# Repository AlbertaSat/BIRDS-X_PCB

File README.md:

# JASPER BIRDS-X PCB
Repository for the PCB design for the JASPER BIRDS-X project.

JASPER is a joint organization between the University of Alberta's AlbertaSat and the University of Calgary's CalgaryToSpace cubesat teams.

## Features
1. Capable of APRS (Automated Packet Reporting System) digipeat and store-and-forward modes, and periodic beaconing, for use by Amateur Radio enthusiasts.
2. Implements a radiation experiment, which compares the radiation shielding properties of shielding options.
	* Uses RADFET sensors as radiation detection sensors.
	* Uses linear CCD sensor (painted black) to sense galactic cosmic rays.
3. Employs power safety systems (over-current protection, enable pins, etc.) to interface with the BIRDS-X satellite parent system.
4. Uses <300 mW on receive, and <1750 mW on transmit.
5. ~~Stores data in flash memory.~~
6. Interfaces with the Mission Boss system via UART.
7. A test fixture board makes flashing and debugging the main payload board easier and more reliable.

## System Block Diagram

## Release Notes
See the [GitHub Releases](https://github.com/AlbertaSat/BIRDS-X_PCB/releases) for this repo.

## License

This repository is licensed under the "CERN Open Hardware Licence Version 2 - Permissive (CERN OHL v2 Permissive)" license. For more information, see [the choosealicense.com description of the license](https://choosealicense.com/licenses/cern-ohl-p-2.0/).

> CERN OHL v2 Permissive
> A permissive license for hardware designs, with conditions only requiring preservation of notices. Contributors provide an express grant of patent rights. Licensed works, modifications, and larger works may be distributed under different terms and without sources.

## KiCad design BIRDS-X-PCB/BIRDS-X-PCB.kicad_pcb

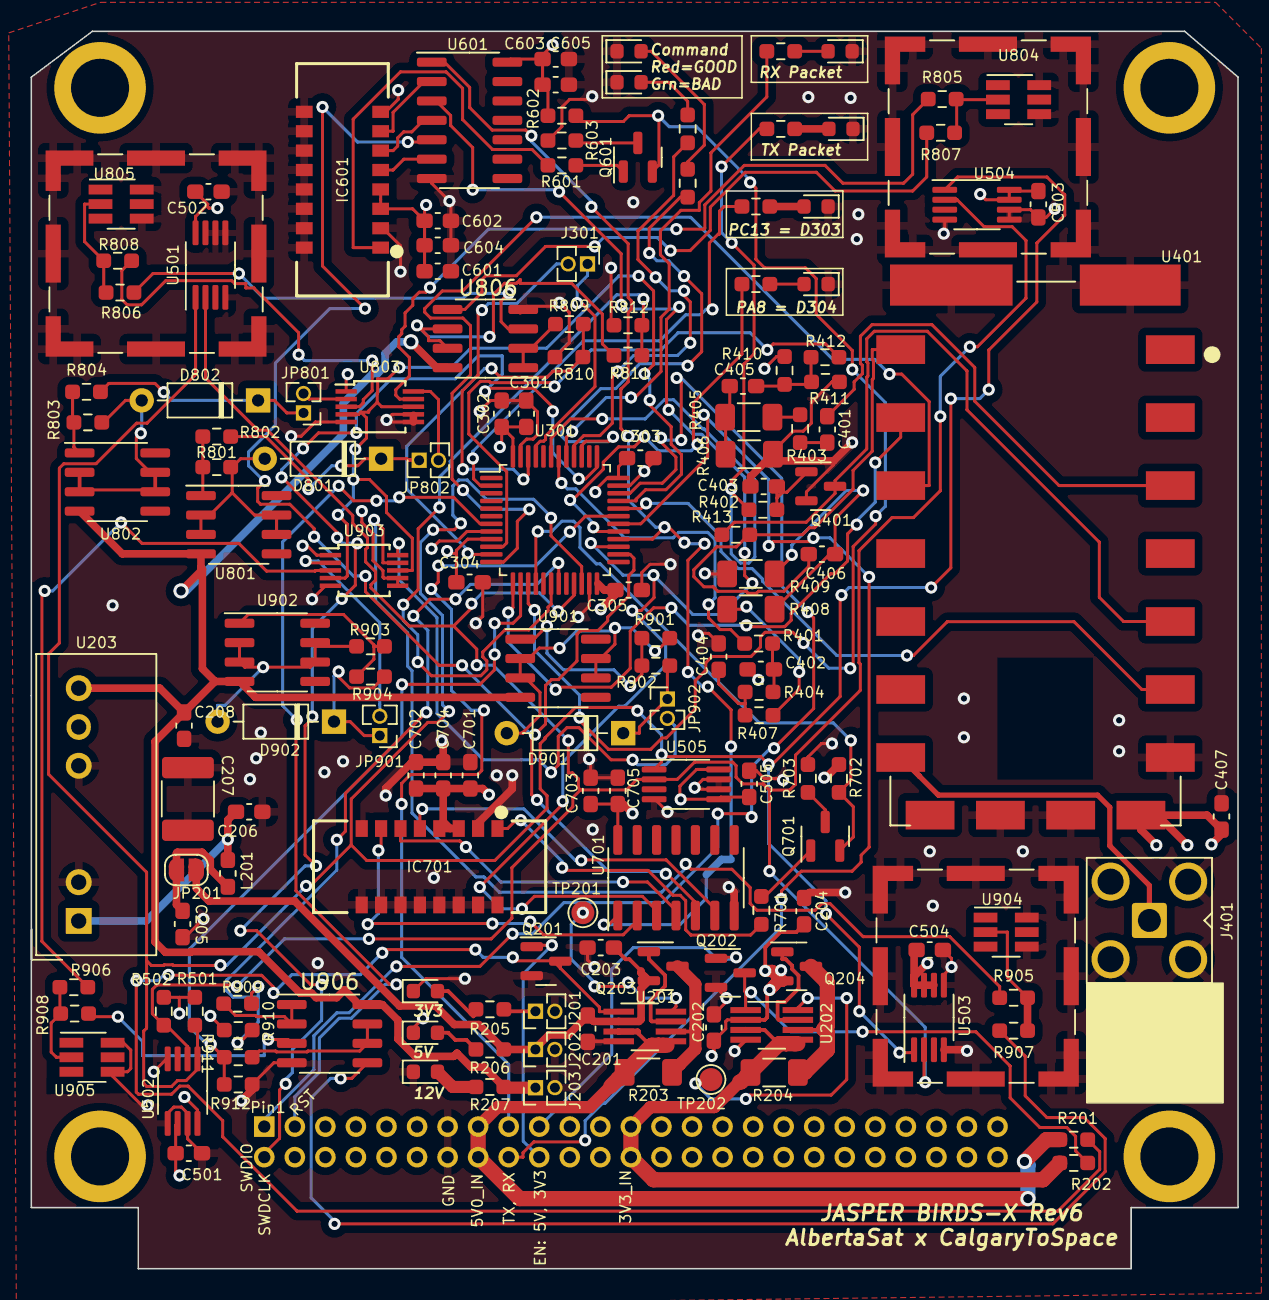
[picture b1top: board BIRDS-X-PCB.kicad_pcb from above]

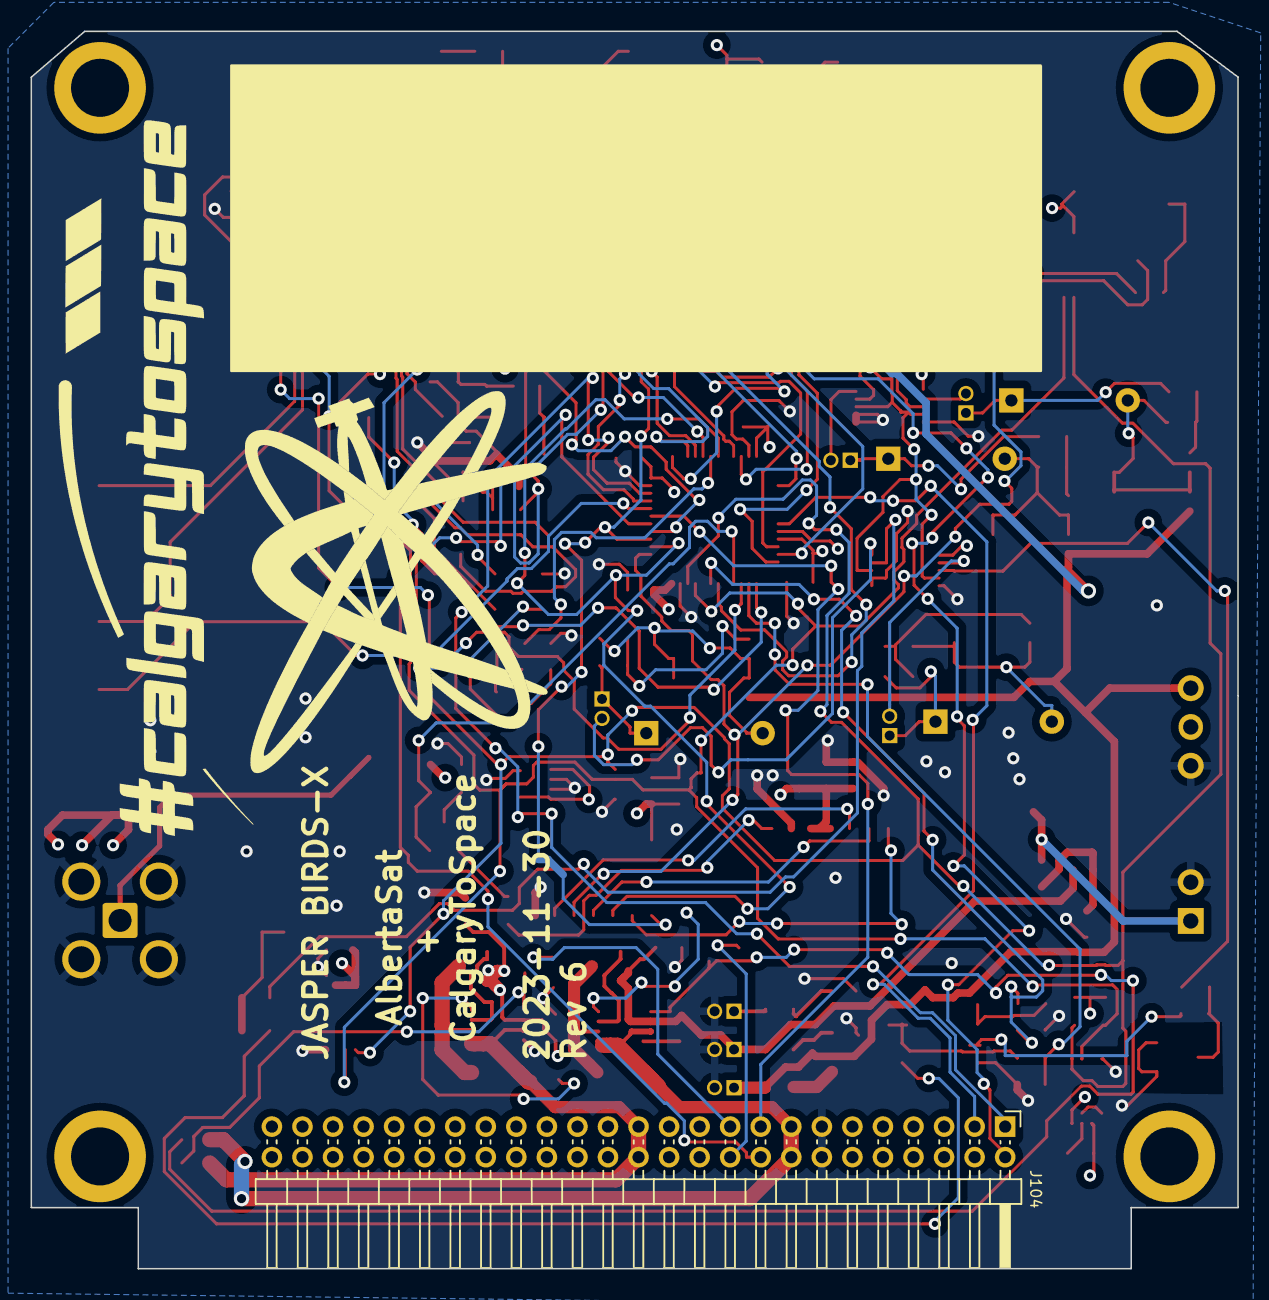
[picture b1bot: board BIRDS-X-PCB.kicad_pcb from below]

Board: 4 copper layers, 79.0 x 81.0 mm, 162 parts (3 on the bottom side), 114 nets.

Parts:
C201, C202, C601, C701: 10u; C_0603_1608Metric_Pad1.08x0.95mm_HandSolder
C203, C204: 1u; C_0603_1608Metric_Pad1.08x0.95mm_HandSolder
C205, C206, C302: 4.7u; C_0603_1608Metric_Pad1.08x0.95mm_HandSolder
C207: 1n; C_1812_4532Metric
C208: 2.2u; C_0603_1608Metric_Pad1.08x0.95mm_HandSolder
C301, C303, C304, C305, C401, C402, C404, C405, C406, C407, C501, C502, C503, C504, C505: 100n; C_0603_1608Metric_Pad1.08x0.95mm_HandSolder
C403: 10n; C_0603_1608Metric_Pad1.08x0.95mm_HandSolder
C602, C603, C702, C703: 0.1u; C_0603_1608Metric_Pad1.08x0.95mm_HandSolder
C604, C605, C704, C705: 0.01u; C_0603_1608Metric_Pad1.08x0.95mm_HandSolder
D201, D202, D203, D301, D302, D303, D304: LED; LED_0603_1608Metric
D801, D802, D901, D902: 1N457; D_DO-35_SOD27_P7.62mm_Horizontal
D_RX301: LED; LED_0603_1608Metric
D_TX301: LED; LED_0603_1608Metric
H101, H102, H103, H104: MountingHole; MountingHole_3.8mm
H105: Logo; AlbertaSat_Logo_25x20mm
H106: Logo; CTS_Logo_50x25mm
IC601, IC701: TCD1103GFG_8Z,AA2_; TCD1103GFG8ZAA2
J101, J102, J103: RFShield_OnePiece; Laird_Technologies_BMI-S-101_13.66x12.70mm
J104: LPC-50M2LG; PinHeader_2x25_P2.00mm_Horizontal
J201, J202, J203, J301: Conn_01x02; PinHeader_1x02_P1.27mm_Vertical
J401: 60611002111501; SMA_Amphenol_901-143_Horizontal_Modified
JP201: Jumper_2_Open; SolderJumper-2_P1.3mm_Open_RoundedPad1.0x1.5mm
JP801, JP802, JP901, JP902: Jumper_2_Open; PinHeader_1x02_P1.27mm_Vertical
L201: 6.8uH; L_0603_1608Metric_Pad1.05x0.95mm_HandSolder
Q201, Q202: 2N7002; SOT-23
Q203, Q204: AO3420; SOT-23
Q401: BC847; SOT-23
Q601, Q701: 2SA1015; SOT-23
R201, R202, R802, R804, R902, R904: 110k; R_0603_1608Metric_Pad0.98x0.95mm_HandSolder
R203: 0.51; R_1206_3216Metric_Pad1.30x1.75mm_HandSolder
R204: 0.075; R_1206_3216Metric_Pad1.30x1.75mm_HandSolder
R205, R501, R502: 3k3; R_0603_1608Metric_Pad0.98x0.95mm_HandSolder
R206: 5.1k; R_0603_1608Metric_Pad0.98x0.95mm_HandSolder
R207: 51k; R_0603_1608Metric_Pad0.98x0.95mm_HandSolder
R301, R302, R305, R306, R309, R310, R413, R602, R702: 2k2; R_0603_1608Metric_Pad0.98x0.95mm_HandSolder
R401, R404: 470; R_0603_1608Metric_Pad0.98x0.95mm_HandSolder
R402: 10k; R_0603_1608Metric_Pad0.98x0.95mm_HandSolder
R403, R805, R806, R807, R808, R905, R906, R907, R908: 0; R_0603_1608Metric_Pad0.98x0.95mm_HandSolder
R405, R406, R408, R409: 10k; R_1206_3216Metric_Pad1.30x1.75mm_HandSolder
R407, R410, R411: 100k; R_0603_1608Metric_Pad0.98x0.95mm_HandSolder
R412: 22k; R_0603_1608Metric_Pad0.98x0.95mm_HandSolder
R601, R603, R701, R703: 150; R_0603_1608Metric_Pad0.98x0.95mm_HandSolder
R801, R803, R901, R903: 11k; R_0603_1608Metric_Pad0.98x0.95mm_HandSolder
R809, R811, R909, R911: 10M; R_0603_1608Metric_Pad0.98x0.95mm_HandSolder
R810, R812, R910, R912: 3.6M; R_0603_1608Metric_Pad0.98x0.95mm_HandSolder
TP201, TP202: TestPoint; TestPoint_Pad_D1.5mm
U201, U202: LTC4361-2; TSOT-23-8_HandSoldering
U203: 0.1S7B_0512S3UP; Converter_DCDC_Gaptec_0.1S7B_3UP_THT
U301: STM32F103C8Tx; LQFP-48_7x7mm_P0.5mm
U401: DRA818V; DORJI_DRA818V
U501, U502, U503, U504, U505: STDS75DS2F; MSOP-8_3x3mm_P0.65mm
U601, U701: 74HC04; SOIC-14_3.9x8.7mm_P1.27mm
U801, U802, U901, U902: LM334M; SOIC-8_3.9x4.9mm_P1.27mm
U803, U903: ADG884xRM; MSOP-10_3x3mm_P0.5mm
U804, U805, U904, U905: VT03; SOT-23-6_Handsoldering
U806, U906: TL972IDR; SOIC-8_3.9x4.9mm_P1.27mm

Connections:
+3V3: C202.1, C204.1, C301.1, C302.1, C303.1, C304.1, C305.1, C407.1, C501.1, C502.1, C503.1, C504.1, C505.1, C601.1, C602.1, C603.1, C604.1, C605.1, C701.1, C702.1, C703.1, C704.1, C705.1, IC601.3 (VAD), IC601.4 (VDD), IC701.3 (VAD), IC701.4 (VDD), J201.1, Q204.2 (S), R205.1, R410.1, R501.1, R502.1, R602.2, R702.2, U202.2 (OUT), U301.9 (VDDA), U301.24 (VDD), U301.36 (VDD), U301.48 (VDD), U401.8 (VBAT), U501.8 (VDD), U502.6 (A1), U502.8 (VDD), U503.6 (A1), U503.7 (A0), U503.8 (VDD), U504.7 (A0), U504.8 (VDD), U505.5 (A2), U505.8 (VDD), U601.14 (VCC), U701.14 (VCC), U803.1 (VDD), U903.1 (VDD)
+5V: C201.1, C203.1, J202.1, JP201.2 (B), Q203.2 (S), R206.1, U201.2 (OUT)
+12V: C208.1, J203.1, R207.1, U203.7 (Vo), U801.4, U802.4, U806.8 (Vcc+), U901.4, U902.4, U906.8 (Vcc+)
/CCD_ICG: U301.27 (PB14), U601.3, U701.3
/CCD_OS1: Q601.2 (E), R602.1, U301.15 (PA5)
/CCD_OS2: Q701.2 (E), R702.1, U301.16 (PA6)
/CCD_PHI_M: U301.26 (PB13), U601.5, U701.5
/CCD_SH: U301.28 (PB15), U601.1, U701.1
/LinearCCD1/ICG_PIN: IC601.6 (ICG), U601.4
/LinearCCD1/OS_PIN: IC601.1 (OS), R601.1
/LinearCCD1/PHI_M_PIN: IC601.5 ([Phi]M), U601.6
/LinearCCD1/SH_PIN: IC601.7 (SH), U601.2
/LinearCCD2/ICG_PIN: IC701.6 (ICG), U701.4
/LinearCCD2/OS_PIN: IC701.1 (OS), R701.1
/LinearCCD2/PHI_M_PIN: IC701.5 ([Phi]M), U701.6
/LinearCCD2/SH_PIN: IC701.7 (SH), U701.2
/MicrocontrollerSheet/AUDIO_DRA_TO_MCU: R412.1, U301.10 (PA0)
/MicrocontrollerSheet/AUDIO_MCU_TO_DRA: R401.1, U301.42 (PB6)
/MicrocontrollerSheet/DRA_PD: U301.32 (PA11), U401.6 (PD)
/MicrocontrollerSheet/I2C_SCL: R502.2, U301.21 (PB10), U501.2 (SCL), U502.2 (SCL), U503.2 (SCL), U504.2 (SCL), U505.2 (SCL)
/MicrocontrollerSheet/I2C_SDA: R501.2, U301.22 (PB11), U501.1 (SDA), U502.1 (SDA), U503.1 (SDA), U504.1 (SDA), U505.1 (SDA)
/MicrocontrollerSheet/PA8_LED: R310.1, U301.29 (PA8)
/MicrocontrollerSheet/PB3_LED_SUCCESS: R301.1, U301.39 (PB3)
/MicrocontrollerSheet/PB4_LED_FAILURE: R306.1, U301.40 (PB4)
/MicrocontrollerSheet/PC13_LED: R309.1, U301.2 (PC13)
/MicrocontrollerSheet/PTT_FROM_MCU: R305.1, R402.1, U301.43 (PB7)
/MicrocontrollerSheet/RFET_EN: U301.33 (PA12), U803.4 (IN1), U803.8 (IN2), U903.4 (IN1), U903.8 (IN2)
/MicrocontrollerSheet/RFET_SENSE_1: R809.2, R810.1, U301.11 (PA1)
/MicrocontrollerSheet/RFET_SENSE_2: R811.2, R812.1, U301.18 (PB0)
/MicrocontrollerSheet/RFET_SENSE_3: R909.2, R910.1, U301.19 (PB1)
/MicrocontrollerSheet/RFET_SENSE_4: R911.2, R912.1, U301.14 (PA4)
/MicrocontrollerSheet/RX_LED: R302.1, U301.41 (PB5)
/MicrocontrollerSheet/UART_DRA_TO_JASPER: U301.13 (PA3), U401.17 (TXD)
/MicrocontrollerSheet/UART_JASPER_TO_DRA: U301.12 (PA2), U401.16 (RXD)
/PowerSheet/3V3_Current_Sense: Q204.3 (D), R204.2, U202.6 (SENSE)
/PowerSheet/5V_Current_Sense: Q203.3 (D), R203.2, U201.6 (SENSE)
/RF_System/AUDIO_FROM_DRA: C401.2, U401.3 (AF_OUT)
/RF_System/AUDIO_TO_DRA: C406.2, R413.2, U401.18 (MIC_IN)
/RF_System/DRA_PTT: Q401.3 (C), R413.1, U401.5 (PTT)
/UART_RX_BOSS_TO_JASPER: J104.17, U301.31 (PA10)
/UART_TX_JASPER_TO_BOSS: J104.18, U301.30 (PA9)
DIO1_3V3_EN_FROM_BOSS: J104.19, Q202.1 (G)
DIO2_5V_EN_FROM_BOSS: J104.20, Q201.1 (G)
GND: C201.2, C202.2, C203.2, C204.2, C205.2, C206.2, C207.1, C207.2, C208.2, C301.2, C302.2, C303.2, C304.2, C305.2, C402.2, C403.2, C404.2, C407.2, C501.2, C502.2, C503.2, C504.2, C505.2, C601.2, C602.2, C603.2, C604.2, C605.2, C701.2, C702.2, C703.2, C704.2, C705.2, D201.1 (K), D202.1 (K), D203.1 (K), D301.1 (K), D302.1 (K), D303.1 (K), D304.1 (K), D_RX301.1 (K), D_TX301.1 (K), IC601.2 (SS), IC601.8 (NC_1), IC601.9 (NC_2), IC601.10 (NC_3), IC601.11 (NC_4), IC601.12 (NC_5), IC601.13 (NC_6), IC601.14 (NC_7), IC601.15 (NC_8), IC601.16 (NC_9), IC701.2 (SS), IC701.8 (NC_1), IC701.9 (NC_2), IC701.10 (NC_3), IC701.11 (NC_4), IC701.12 (NC_5), IC701.13 (NC_6), IC701.14 (NC_7), IC701.15 (NC_8), IC701.16 (NC_9), J101.1 (Shield), J102.1 (Shield), J103.1 (Shield), J104.13, J104.14, J201.2, J202.2, J203.2, J401.2 (Ext), Q201.2 (S), Q202.2 (S), Q401.2 (E), R406.1, R409.1, R411.2, R603.2, R703.2, R810.2, R812.2, R910.2, R912.2, U201.4 (GND), U202.4 (GND), U203.2 (GND), U203.5 (0V/-Vo), U301.8 (VSSA), U301.23 (VSS), U301.35 (VSS), U301.47 (VSS), U401.7 (H/L), U401.9 (GND_1), U401.10 (GND_2), U401.P2 (GND_P2), U401.P3 (GND_P3), U501.4 (GND), U501.5 (A2), U501.6 (A1), U501.7 (A0), U502.4 (GND), U502.5 (A2), U502.7 (A0), U503.4 (GND), U503.5 (A2), U504.4 (GND), U504.5 (A2), U504.6 (A1), U505.4 (GND), U505.6 (A1), U505.7 (A0), U601.7 (GND), U701.7 (GND), U803.5 (S1B), U803.6 (GND), U803.7 (S2B), U804.4 (GATE), U804.6 (DRAIN), U805.4 (GATE), U805.6 (DRAIN), U806.4 (Vcc-), U903.5 (S1B), U903.6 (GND), U903.7 (S2B), U904.4 (GATE), U904.6 (DRAIN), U905.4 (GATE), U905.6 (DRAIN), U906.4 (Vcc-)
unnamed: C401.1, R403.2
unnamed: C402.1, R401.2, R404.1
unnamed: C404.1, R404.2, R407.1
unnamed: C405.1, R405.1, R406.2
unnamed: C405.2, R410.2, R411.1, R412.2
unnamed: C406.1, R408.1, R409.2
unnamed: D201.2 (A), R205.2
unnamed: D202.2 (A), R206.2
unnamed: D203.2 (A), R207.2
unnamed: D301.2 (A), R301.2
unnamed: D302.2 (A), R306.2
unnamed: D303.2 (A), R309.2
unnamed: D304.2 (A), R310.2
unnamed: D801.2 (A), R801.2, U801.2, U801.3, U801.6, U801.7
unnamed: D801.1 (K), JP802.1 (A), R802.2
unnamed: D802.2 (A), R803.2, U802.2, U802.3, U802.6, U802.7
unnamed: D802.1 (K), JP801.1 (A), R804.2
unnamed: D901.2 (A), R901.2, U901.2, U901.3, U901.6, U901.7
unnamed: D901.1 (K), JP902.1 (A), R902.2
unnamed: D902.2 (A), R903.2, U902.2, U902.3, U902.6, U902.7
unnamed: D902.1 (K), JP901.1 (A), R904.2
unnamed: D_RX301.2 (A), R302.2
unnamed: D_TX301.2 (A), R305.2
unnamed: J301.1, U301.45 (PB8)
unnamed: J301.2, U301.46 (PB9)
unnamed: J401.1 (In), U401.12 (ANT)
unnamed: C205.1, JP201.1 (A), L201.1
unnamed: JP801.2 (B), U803.2 (S1A)
unnamed: JP802.2 (B), U803.10 (S2A)
unnamed: JP901.2 (B), U903.2 (S1A)
unnamed: JP902.2 (B), U903.10 (S2A)
unnamed: Q201.3 (D), R201.2, U201.1 (~ON)
unnamed: Q202.3 (D), R202.2, U202.1 (~ON)
unnamed: Q203.1 (G), U201.7 (GATE)
unnamed: Q204.1 (G), U202.7 (GATE)
unnamed: C403.1, Q401.1 (B), R402.2
unnamed: Q601.1 (B), R601.2
unnamed: Q601.3 (C), R603.1
unnamed: Q701.1 (B), R701.2
unnamed: Q701.3 (C), R703.1
unnamed: R403.1, R405.2
unnamed: R407.2, R408.2
unnamed: R801.1, R802.1, U801.1
unnamed: R803.1, R804.1, U802.1
unnamed: R901.1, R902.1, U901.1
unnamed: R903.1, R904.1, U902.1
unnamed: TP201.1, U201.8 (~PWRGD)
unnamed: TP202.1, U202.8 (~PWRGD)
unnamed: C206.1, L201.2, U203.1 (Vin)
unnamed: R806.1, U803.3 (D1)
unnamed: R805.1, U803.9 (D2)
unnamed: R805.2, R807.1, U804.2 (SOURCE_BULK)
unnamed: R806.2, R808.1, U805.2 (SOURCE_BULK)
unnamed: R808.2, U806.3 (+)
unnamed: R809.1, U806.1, U806.2 (-)
unnamed: R807.2, U806.5 (+)
unnamed: R811.1, U806.6 (-), U806.7
unnamed: R906.1, U903.3 (D1)
unnamed: R905.1, U903.9 (D2)
unnamed: R905.2, R907.1, U904.2 (SOURCE_BULK)
unnamed: R906.2, R908.1, U905.2 (SOURCE_BULK)
unnamed: R908.2, U906.3 (+)
unnamed: R909.1, U906.1, U906.2 (-)
unnamed: R907.2, U906.5 (+)
unnamed: R911.1, U906.6 (-), U906.7
ST_RST: J104.3, U301.7 (NRST)
ST_SWDCLK: J104.2, U301.37 (PA14)
ST_SWDIO: J104.1, U301.34 (PA13)
SUP_3V3_2: J104.25, J104.26, R202.1, R204.1, U202.3 (GATEP), U202.5 (IN)
SUP_5V0: J104.15, J104.16, R201.1, R203.1, U201.3 (GATEP), U201.5 (IN)

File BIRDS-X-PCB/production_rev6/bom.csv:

Designator,Footprint,Quantity,Value,LCSC Part #
"C201, C202, C601, C701",0603,4,10u,
"C203, C204",0603,2,1u,
"C205, C206, C302",0603,3,4.7u,
C208,0603,1,2.2u,
"C301, C303, C304, C305, C401, C402, C404, C405, C406, C407, C501, C502, C503, C504, C505",0603,15,100n,
C403,0603,1,10n,
"C602, C603, C702, C703",0603,4,0.1u,
"C604, C605, C704, C705",0603,4,0.01u,
"D201, D202, D203, D301, D304, D_RX301, D_TX301",0603,7,LED,C93128
"D302, D303",0603,2,LED,C375577
"D801, D802, D901, D902",D_DO-35_SOD27_P7.62mm_Horizontal,4,1N457,
"H101, H102, H103, H104",MountingHole_3.8mm,4,MountingHole,
H105,AlbertaSat_Logo_25x20mm,1,Logo,
H106,CTS_Logo_50x25mm,1,Logo,
"IC601, IC701",TCD1103GFG8ZAA2,2,"TCD1103GFG_8Z,AA2_",
"J101, J102, J103",Laird_Technologies_BMI-S-101_13.66x12.70mm,3,RFShield_OnePiece,
J104,PinHeader_2x25_P2.00mm_Horizontal,1,LPC-50M2LG,
J401,SMA_Amphenol_901-143_Horizontal_Modified,1,60611002111501,
JP201,SolderJumper-2_P1.3mm_Open_RoundedPad1.0x1.5mm,1,Jumper_2_Open,
L201,0603,1,6.8uH,
"Q201, Q202",SOT-23,2,2N7002,C3290044
"Q203, Q204",SOT-23,2,AO3420,
Q401,SOT-23,1,BC847,C475630
"Q601, Q701",SOT-23,2,2SA1015,C5189099
"R201, R202, R802, R804, R902, R904",0603,6,110k,
R203,1206,1,0.51,C104948
R204,1206,1,0.075,C171394
"R205, R501, R502",0603,3,3k3,
R206,0603,1,5.1k,
R207,0603,1,51k,
"R301, R302, R305, R306, R309, R310, R602, R702",0603,8,2k2,
"R401, R404",0603,2,470,
R402,0603,1,10k,
"R403, R805, R806, R807, R808, R905, R906, R907, R908",0603,9,0,
"R405, R408",1206,2,10k,
"R407, R410, R411",0603,3,100k,
R412,0603,1,22k,
"R601, R603, R701, R703",0603,4,150,
"R801, R803, R901, R903",0603,4,11k,
"R809, R811, R909, R911",0603,4,10M,
"R810, R812, R910, R912",0603,4,3.6M,
"TP201, TP202",TestPoint_Pad_D1.5mm,2,TestPoint,
"U201, U202",TSOT-23-8_HandSoldering,2,LTC4361-2,
U203,Converter_DCDC_Gaptec_0.1S7B_3UP_THT,1,0.1S7B_0512S3UP,
U301,LQFP-48_7x7mm_P0.5mm,1,STM32F103C8Tx,C8734
U401,DORJI_DRA818V,1,DRA818V,
"U501, U502, U503, U504, U505",MSOP-8_3x3mm_P0.65mm,5,STDS75DS2F,C283289
"U601, U701",SOIC-14_3.9x8.7mm_P1.27mm,2,74HC04,C86613
"U801, U802, U901, U902",SOIC-8_3.9x4.9mm_P1.27mm,4,LM334M,C140388
"U803, U903",MSOP-10_3x3mm_P0.5mm,2,ADG884xRM,C143911
"U804, U805, U904, U905",SOT-23-6_Handsoldering,4,VT03,
"U806, U906",SOIC-8_3.9x4.9mm_P1.27mm,2,TL972IDR,C46127

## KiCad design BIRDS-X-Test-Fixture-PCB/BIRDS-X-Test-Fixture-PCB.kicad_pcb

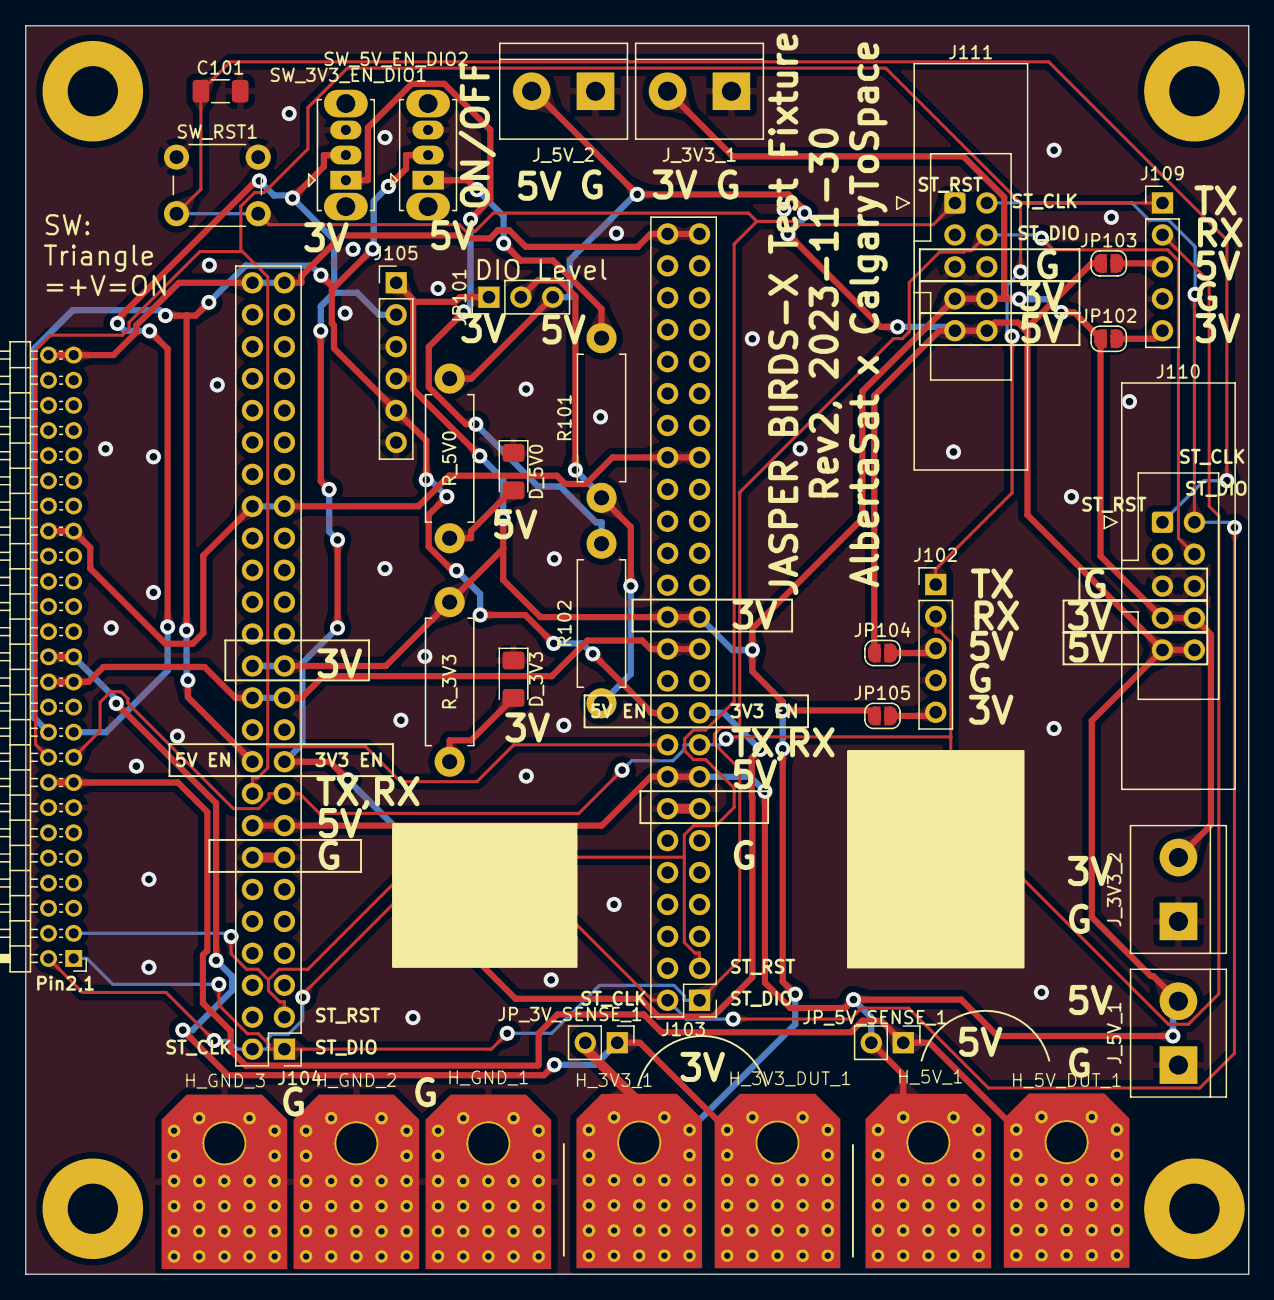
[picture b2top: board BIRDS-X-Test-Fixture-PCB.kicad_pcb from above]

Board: 2 copper layers, 97.3 x 99.3 mm, 40 parts (0 on the bottom side), 24 nets.

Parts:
C101: 100n; C_1206_3216Metric_Pad1.33x1.80mm_HandSolder
D_3V3, D_5V0: LED; LED_1206_3216Metric_Pad1.42x1.75mm_HandSolder
H1, H2, H3, H4: MountingHole; MountingHole_4mm_Pad
H_3V3_1, H_3V3_DUT_1, H_5V_1, H_5V_DUT_1: MountingHole_Pad; EdgeAlligatorConnector
H_GND_1, H_GND_2, H_GND_3: MountingHole_Pad; EdgeAlligatorConnector
J101: LPC-50M2LG; PinHeader_2x25_P2.00mm_Horizontal
J102, J109: Conn_01x05; PinHeader_1x05_P2.54mm_Vertical
J103, J104: PinHeader_2x25_P2.54mm_Vertical
J105: Conn_01x06; PinHeader_1x06_P2.54mm_Vertical
J110, J111: Conn_02x05_Odd_Even; IDC-Header_2x05_P2.54mm_Latch_Vertical
JP101: Jumper_3_Open; PinHeader_1x03_P2.54mm_Vertical
JP102, JP103, JP104, JP105: SolderJumper_2_Open; SolderJumper-2_P1.3mm_Open_RoundedPad1.0x1.5mm
JP_3V_SENSE_1, JP_5V_SENSE_1: Jumper_2_Bridged; PinHeader_1x02_P2.54mm_Vertical
J_3V3_1, J_3V3_2, J_5V_1, J_5V_2: Screw_Terminal_01x02; TerminalBlock_bornier-2_P5.08mm
R101, R102: 1k; R_Axial_DIN0411_L9.9mm_D3.6mm_P12.70mm_Horizontal
R_3V3: 1k; R_Axial_DIN0411_L9.9mm_D3.6mm_P12.70mm_Horizontal
R_5V0: 2.2k; R_Axial_DIN0411_L9.9mm_D3.6mm_P12.70mm_Horizontal
SW_3V3_EN_DIO1, SW_5V_EN_DIO2: SW_SPDT; SW_Slide_1P2T_CK_OS102011MS2Q
SW_RST1: SW_Push; SW_PUSH_6mm

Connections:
/3V3_DUT: H_3V3_DUT_1.1, J101.25, J101.26, JP_3V_SENSE_1.1 (A)
/5V_DUT: H_5V_DUT_1.1, J101.15, J101.16, JP_5V_SENSE_1.1 (A)
/UART_RX_BOSS_TO_JASPER: J101.17, J102.2, J103.17, J104.17, J109.2
/UART_TX_JASPER_TO_BOSS: J101.18, J102.1, J103.18, J104.18, J109.1
DIO1_3V3_EN_FROM_BOSS: J101.19, J103.19, J104.19, J105.2, SW_3V3_EN_DIO1.2 (B)
DIO2_5V_EN_FROM_BOSS: J101.20, J103.20, J104.20, J105.5, SW_5V_EN_DIO2.2 (B)
GND: C101.2, D_3V3.1 (K), D_5V0.1 (K), H_GND_1.1, H_GND_2.1, H_GND_3.1, J101.13, J101.14, J102.4, J103.13, J103.14, J104.13, J104.14, J105.3, J105.6, J109.4, J110.5, J110.6, J111.5, J111.6, J_3V3_1.1, J_3V3_2.1, J_5V_1.1, J_5V_2.1, SW_3V3_EN_DIO1.3 (C), SW_5V_EN_DIO2.3 (C), SW_RST1.1
unnamed: D_3V3.2 (A), R_3V3.2
unnamed: D_5V0.2 (A), R_5V0.2
unnamed: J102.3, JP104.2 (B)
unnamed: J102.5, JP105.2 (B)
unnamed: J109.3, JP103.2 (B)
unnamed: J109.5, JP102.2 (B)
unnamed: JP101.2 (C), R101.1, R102.1
unnamed: R102.2, SW_3V3_EN_DIO1.1 (A)
unnamed: R101.2, SW_5V_EN_DIO2.1 (A)
ST_RST: C101.1, J101.3, J103.3, J104.3, J110.1, J111.1, SW_RST1.2
ST_SWDCLK: J101.2, J103.2, J104.2, J110.2, J111.2
ST_SWDIO: J101.1, J103.1, J104.1, J110.4, J111.4
SUP_3V3_1: J101.49, J101.50, J103.49, J103.50, J104.49, J104.50
SUP_3V3_2: H_3V3_1.1, J103.25, J103.26, J104.25, J104.26, J105.1, J105.4, J110.7, J110.8, J111.7, J111.8, JP101.1 (A), JP102.1 (A), JP105.1 (A), JP_3V_SENSE_1.2 (B), J_3V3_1.2, J_3V3_2.2, R_3V3.1
SUP_5V0: H_5V_1.1, J103.15, J103.16, J104.15, J104.16, J110.9, J110.10, J111.9, J111.10, JP101.3 (B), JP103.1 (A), JP104.1 (A), JP_5V_SENSE_1.2 (B), J_5V_1.2, J_5V_2.2, R_5V0.1
SUP_UNREG_1: J101.23, J101.24, J103.23, J103.24, J104.23, J104.24
SUP_UNREG_2: J101.35, J101.36, J103.35, J103.36, J104.35, J104.36

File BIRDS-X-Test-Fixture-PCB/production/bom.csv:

Designator,Footprint,Quantity,Value,LCSC Part #
C101,1206,1,100n,
"D_3V3, D_5V0",1206,2,LED,
"H1, H2, H3, H4",MountingHole_4mm_Pad,4,MountingHole,
"H_3V3_1, H_3V3_DUT_1, H_5V_1, H_5V_DUT_1, H_GND_1, H_GND_2, H_GND_3",MountingHole_4mm_Pad_Via,7,MountingHole_Pad,
J101,PinHeader_2x25_P2.00mm_Horizontal,1,LPC-50M2LG,
"J102, J109",PinHeader_1x05_P2.54mm_Vertical,2,Conn_01x05,
"J103, J104",PinHeader_2x25_P2.54mm_Vertical,2,~,
J105,PinHeader_1x06_P2.54mm_Vertical,1,Conn_01x06,
"J110, J111",IDC-Header_2x05_P2.54mm_Latch_Vertical,2,Conn_02x05_Odd_Even,
JP101,PinHeader_1x03_P2.54mm_Vertical,1,Jumper_3_Open,
"JP_3V_SENSE_1, JP_5V_SENSE_1",TestPoint_2Pads_Pitch2.54mm_Drill0.8mm,2,Jumper_2_Bridged,
"J_3V3_1, J_3V3_2, J_5V_1, J_5V_2",TerminalBlock_bornier-2_P5.08mm,4,Screw_Terminal_01x02,
R_3V3,R_Axial_DIN0411_L9.9mm_D3.6mm_P12.70mm_Horizontal,1,1k,
R_5V0,R_Axial_DIN0411_L9.9mm_D3.6mm_P12.70mm_Horizontal,1,2.2k,
"SW_3V3_EN_DIO1, SW_5V_EN_DIO2",SW_Slide_1P2T_CK_OS102011MS2Q,2,SW_SPDT,
SW_RST1,SW_PUSH_6mm,1,SW_Push,

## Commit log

2023-03-26 Add radfet symbol, schematic pages
2023-03-27 Fix gitignore
2023-04-01 Added microcontroller circuitry
2023-04-06 Migrate libraries, create LTC4361 symbol
2023-04-06 Finish power OCP
2023-04-06 Add MTT4B footprint
2023-04-06 Bug fix
2023-04-06 Add more components
2023-04-09 Add flash, temperature sensor, etc.
2023-04-09 Add BOM and footprints
2023-04-11 Added current source circuitry for RADFET Readout
2023-04-12 Completed MCU & Experiment Circuit
2023-04-12 Fixed voltage dividers
2023-04-13 Add TODO and update PDF
2023-04-15 Added RFET enabling connections
2023-04-16 Semantic and symbol updates, begin review changes
2023-04-16 MCU pin assignment review
2023-04-16 Add more MCU changes
2023-04-16 Implement oscillator improvements
2023-04-16 Add logic level converters, etc.
2023-04-16 Fix power enable issue
2023-04-16 Add footprints
2023-04-16 Finish footprints assignment
2023-04-16 Prep for layout
2023-04-16 Add core restricted layouts and lock them
2023-04-16 Fix flash signals, fix footprints
2023-04-20 Add notes from schematic review session
2023-04-22 Finish layout
2023-04-22 Update footprint
2023-04-22 Update tempo current source
2023-04-22 Do some routing
2023-04-22 Route more, move MCU
2023-04-23 PCB update
2023-04-23 PCB updated
2023-04-23 Fix DRC issues
2023-04-23 Finish fixing DRC issues, except power lines
2023-04-23 Route power lines on 2-layer board, if desired
2023-04-23 Minor layout changes to consolodate ground planes
2023-04-23 Add silkscreen labels
2023-04-23 Move 3v3 and 5v lines to polygon pour layers
2023-04-23 Re-route power lines from input to protection
2023-04-28 Update resistor vals, plot, BOM
2023-04-28 Update copper anulus on mounting holes
2023-04-28 Add logos and final labels
2023-04-29 Final changes for rev1
2023-04-29 Add teardrops
2023-04-29 Export gerbers
2023-04-29 Add text silk screen areas
2023-04-29 Export gerber
2023-05-28 Update release notes
2023-05-28 Remove all Rev1.0 gerbers
2023-06-09 RF System updated
2023-06-13 Rename Experiment to RadfetExperiment
2023-06-13 Add PIN Diode experiment
2023-06-13 Update footprint assignments
2023-06-13 Update footprints to 0603
2023-06-13 Do major layout
2023-06-13 Re-organize PIN diode sheet structure
2023-06-13 Continue layout and routing
2023-06-14 Add MCU assignments, RF annotations per ref design, heirarchal pins
2023-06-14 Finish most routing
2023-06-16 Move around silkscreens for final production
2023-06-16 Add EMC protection for 12V step-up
2023-06-16 Add semi-random radiation shielding mounting holes
2023-06-18 Implement Liam's suggstions, move vias out of pads
2023-06-20 Update pins and LCSC part numbers
2023-06-21 Add final Rev2 production files
2023-06-22 Add LCSC LM334 part number for next time, remove point-in-time files
2023-07-21 Redefine edge cuts, holes, stack header
2023-07-21 Add NucleoTNC schematic copy
2023-07-21 Clean up NucleoTNC
2023-07-21 Update parts in RF system
2023-07-21 Add DRA818V content
2023-07-22 Re-arrange MCU
2023-07-23 Change temperature sensor
2023-07-23 Schematic and PCB files updated with new filter
2023-07-23 Adjusted the filter from PA_BOOST
    C28: 2.7p, L8: 430n, C32: 180p, L10: 6.8n
2023-07-23 Finish double MCU re-org
2023-07-23 Restore old microcontroller setup
2023-07-23 Clean up heirarchy
2023-07-24 Tweaks
2023-07-24 Finish MCU pin assignments for UART/I2C
2023-07-24 Schematic updates
2023-07-24 Assign remaining footprints, fix Annotations
2023-07-24 Major layout
2023-07-24 Do most of routing
2023-07-24 DRC vias everywhere
2023-07-24 Fix all DRC
2023-07-24 Done Rev3
2023-07-24 Add rev3 JLC production files
2023-08-22 Update inverter resistors, add TPs
2023-08-22 Refactor jumper for PIN experiment power
2023-08-22 Start test fixture PCB
2023-08-22 Done test fixture schematic
2023-08-22 Layout and label PCB
2023-08-22 Finish test fixture
2023-08-22 Add 12V disable
2023-08-22 Update labels on test fixture
2023-08-22 Route a bit
2023-08-22 Update to new STM32F103 MCU
2023-08-22 Finish PCB layout
2023-08-22 Fix logo
2023-08-23 Welp
2023-08-23 Bigger welp
2023-08-23 Revert "Bigger welp"
    This reverts commit 0054a0e7b2f6f9c4b8ea2502b56168c89fe4c559.
2023-08-23 Revert "Welp"
    This reverts commit 5da3a1a40cdef91cfc9ebce7a6f18400f4c29f94.
2023-08-23 Release Rev4
2023-08-23 Improve Rev4 docs
2023-08-24 Fix missing connections, release Rev5.0
2023-09-03 Added CAD model and component models
2023-09-07 Prep docs for Rev5.1 release
2023-09-11 Tiny silkscreen tweaks
2023-11-13 Remove external crystals
2023-11-13 Remove PIN diode experiment
2023-11-13 Update routing and renderings
2023-11-13 Minor DRC fixes
2023-11-19 Clean up silkscreen labels
2023-11-27 Add CCD model, reorganize 3D models
2023-11-27 Update schematics with LinearCCDs, remove flash
2023-11-27 Layout and route a bit
2023-11-27 Fix up broken bits
2023-11-29 Autoroute a few remaining parts
2023-11-29 Schematic re-work (esp. RADFET fixes)
2023-11-29 Layout PCB
2023-11-29 Route thick power nets
2023-11-30 Add resistors to switch part
2023-11-30 Do some routing, plot PDF
2023-11-30 Route board
2023-11-30 Fix BJT on CCD circuit
2023-11-30 Update test fixture board
2023-11-30 Finish routing test fixture board
2023-11-30 Touch up test fixture board
2023-11-30 Generate test fixture gerber
2023-11-30 Update test fixture schematic PDF
2023-12-01 Prep and save Rev6 export
2023-12-03 Set hidden state on header pins in render
2023-12-03 Minor docs updates
2023-12-14 Test fixture - update resistor values, add stand offs
2023-12-25 Tiny note change
2023-12-29 Reposition label
2024-02-28 Add CERN OHL v2 Permissive license
2024-02-28 Update image link in README
2024-02-28 Update image link in README (#3)
